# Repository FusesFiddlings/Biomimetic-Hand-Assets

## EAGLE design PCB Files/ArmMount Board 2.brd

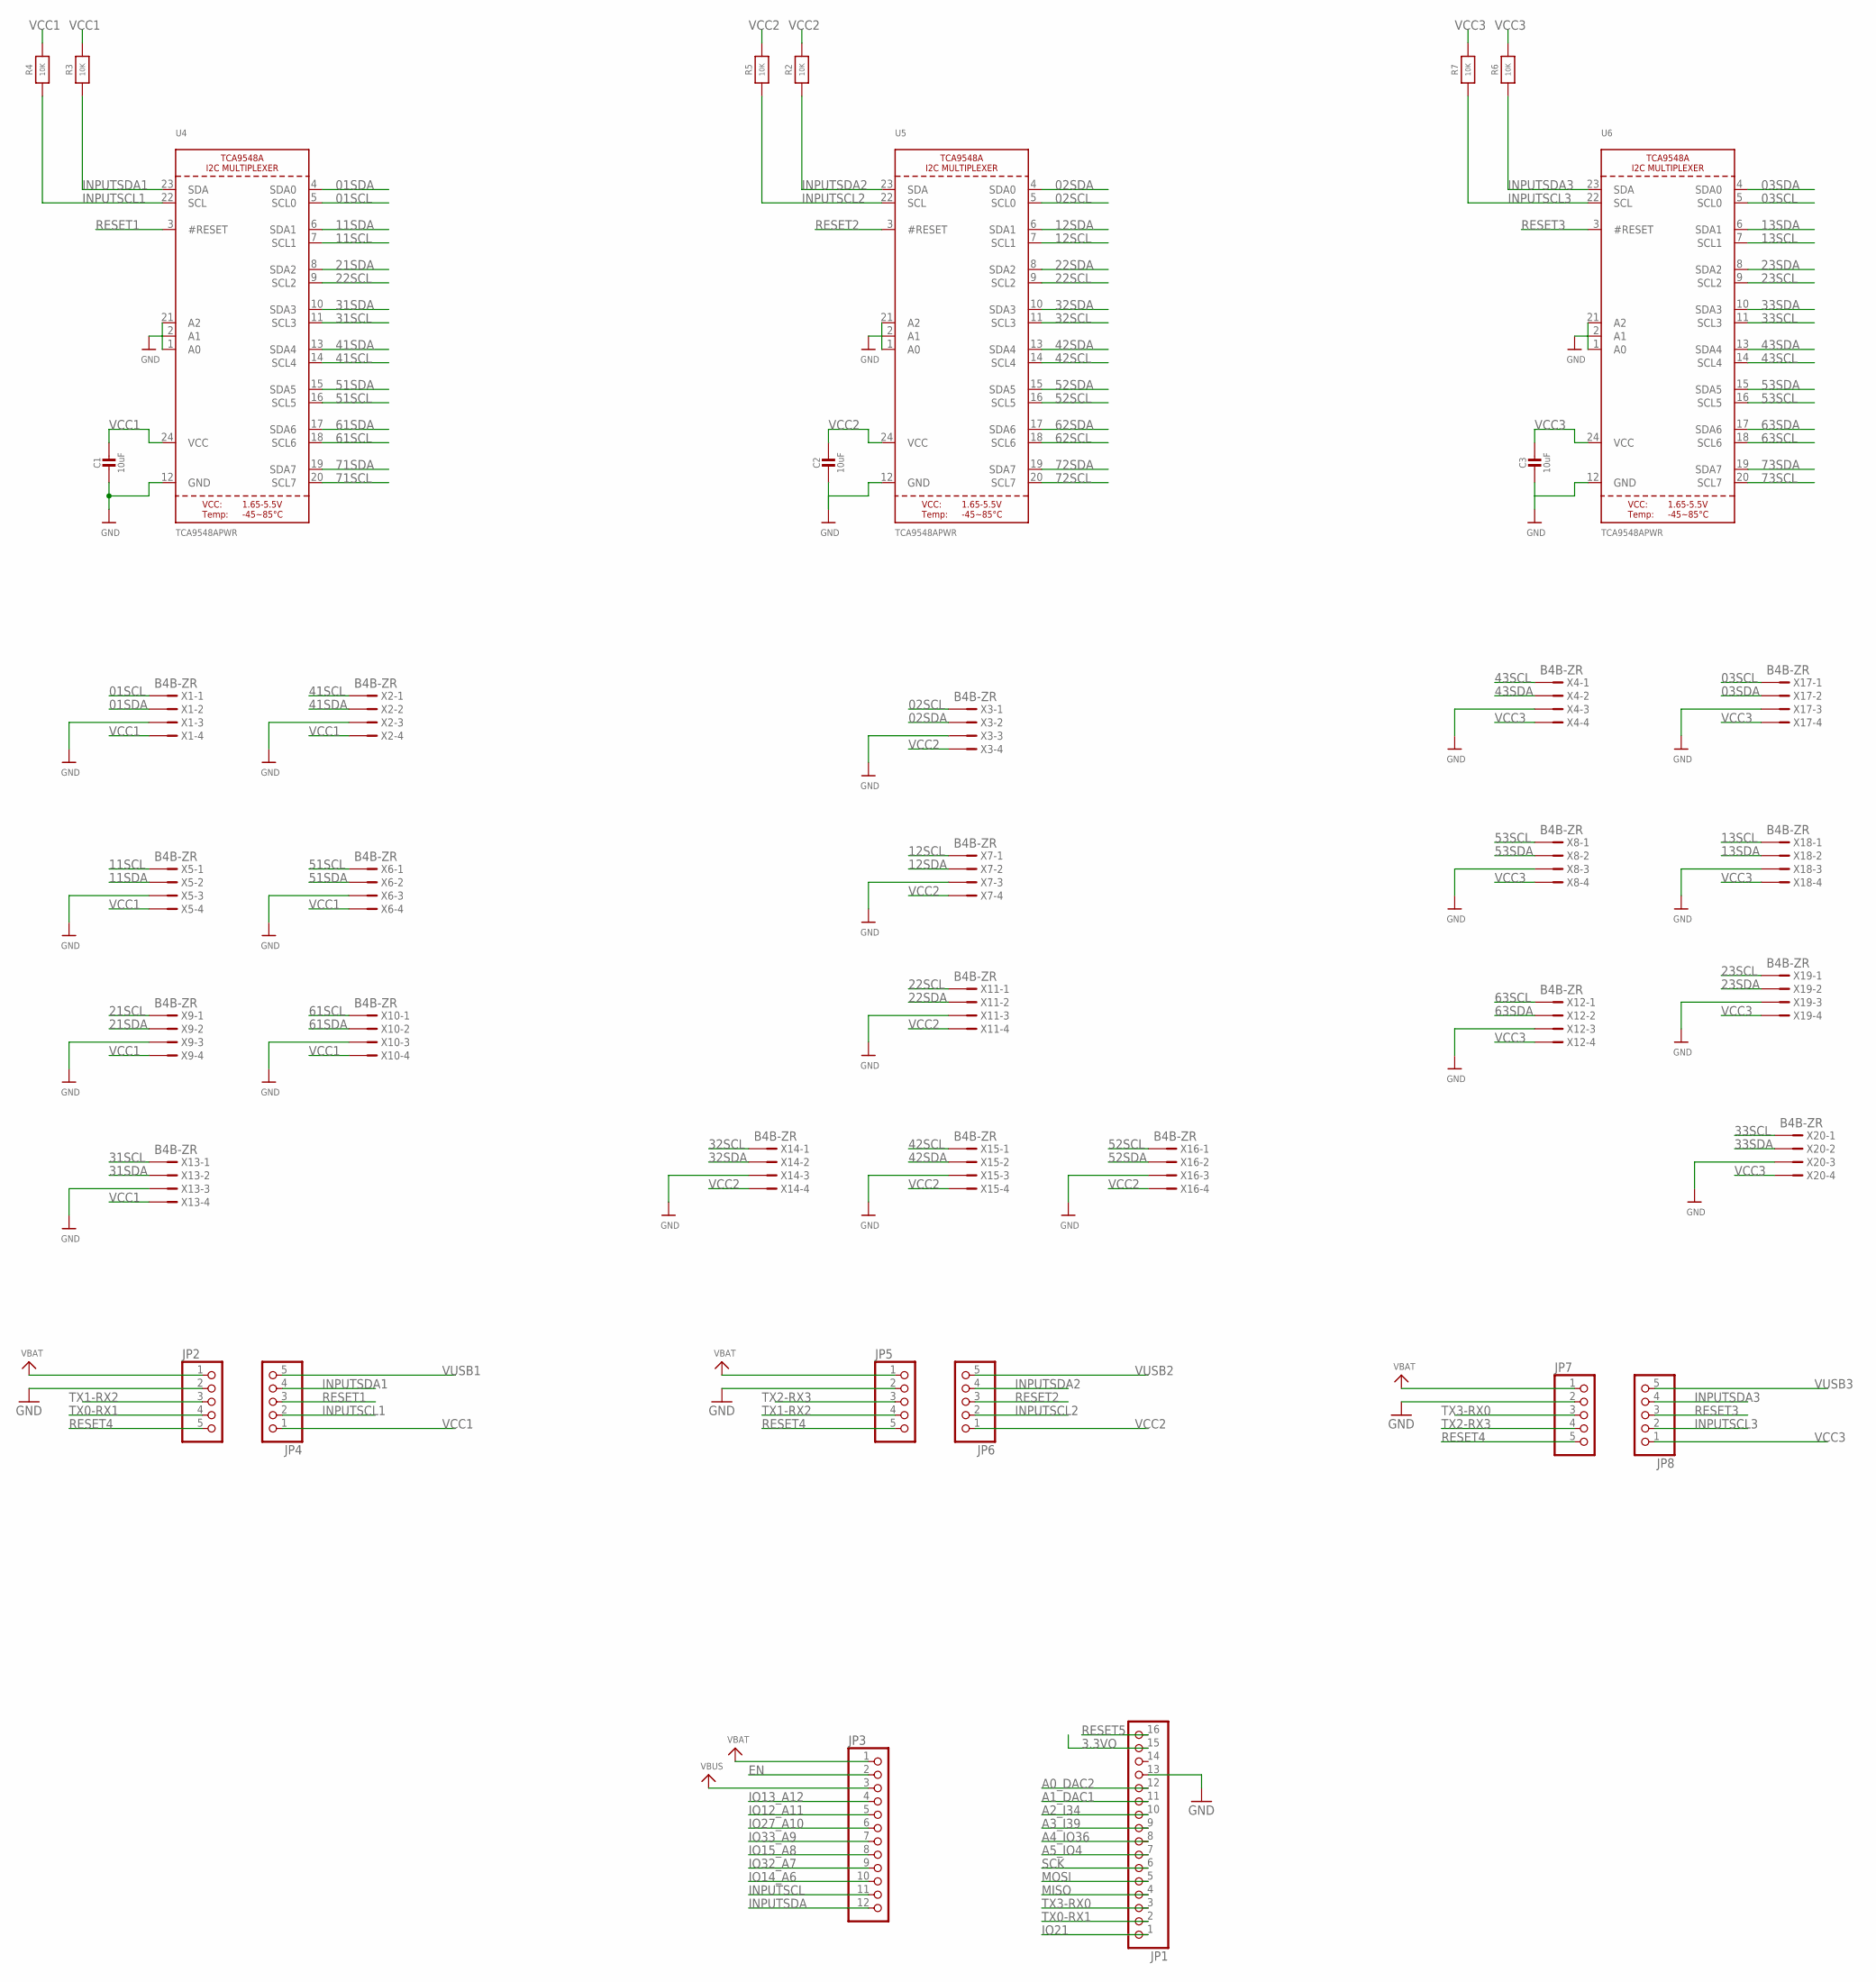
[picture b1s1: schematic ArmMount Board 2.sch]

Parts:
C1, C2, C3: 10uF; 0805-NO
JP1: HEADER-1X16_MIN; 1X16_ROUND_MIN
JP2, JP4, JP5, JP6, JP7, JP8: HEADER-1X576MIL; 1X05_ROUND_76
JP3: HEADER-1X12_MIN; 1X12_ROUND_MIN
R2, R3, R4, R5, R6, R7: 10K; 0805-NO
U4, U5, U6: TCA9548APWR; TSSOP24
X1, X2, X3, X4, X5, X6, X7, X8, X9, X10, X11, X12, X13, X14, X15, X16, X17, X18, X19, X20: B4B-ZR

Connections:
01SCL: U4.5 (SCL0), X1.1
01SDA: U4.4 (SDA0), X1.2
02SCL: U5.5 (SCL0), X3.1
02SDA: U5.4 (SDA0), X3.2
3.3VO: JP1.15
03SCL: U6.5 (SCL0), X17.1
03SDA: U6.4 (SDA0), X17.2
11SCL: U4.7 (SCL1), X5.1
11SDA: U4.6 (SDA1), X5.2
12SCL: U5.7 (SCL1), X7.1
12SDA: U5.6 (SDA1), X7.2
13SCL: U6.7 (SCL1), X18.1
13SDA: U6.6 (SDA1), X18.2
21SCL: X9.1
21SDA: U4.8 (SDA2), X9.2
22SCL: U4.9 (SCL2), U5.9 (SCL2), X11.1
22SDA: U5.8 (SDA2), X11.2
23SCL: U6.9 (SCL2), X19.1
23SDA: U6.8 (SDA2), X19.2
31SCL: U4.11 (SCL3), X13.1
31SDA: U4.10 (SDA3), X13.2
32SCL: U5.11 (SCL3), X14.1
32SDA: U5.10 (SDA3), X14.2
33SCL: U6.11 (SCL3), X20.1
33SDA: U6.10 (SDA3), X20.2
41SCL: U4.14 (SCL4), X2.1
41SDA: U4.13 (SDA4), X2.2
42SCL: U5.14 (SCL4), X15.1
42SDA: U5.13 (SDA4), X15.2
43SCL: U6.14 (SCL4), X4.1
43SDA: U6.13 (SDA4), X4.2
51SCL: U4.16 (SCL5), X6.1
51SDA: U4.15 (SDA5), X6.2
52SCL: U5.16 (SCL5), X16.1
52SDA: U5.15 (SDA5), X16.2
53SCL: U6.16 (SCL5), X8.1
53SDA: U6.15 (SDA5), X8.2
61SCL: U4.18 (SCL6), X10.1
61SDA: U4.17 (SDA6), X10.2
62SCL: U5.18 (SCL6)
62SDA: U5.17 (SDA6)
63SCL: U6.18 (SCL6), X12.1
63SDA: U6.17 (SDA6), X12.2
71SCL: U4.20 (SCL7)
71SDA: U4.19 (SDA7)
72SCL: U5.20 (SCL7)
72SDA: U5.19 (SDA7)
73SCL: U6.20 (SCL7)
73SDA: U6.19 (SDA7)
A0_DAC2: JP1.12
A1_DAC1: JP1.11
A2_I34: JP1.10
A3_I39: JP1.9
A4_IO36: JP1.8
A5_IO4: JP1.7
EN: JP3.2
GND: C1.2, C2.2, C3.2, JP1.13, JP2.2, JP5.2, JP7.2, U4.1 (A0), U4.2 (A1), U4.12 (GND), U4.21 (A2), U5.1 (A0), U5.2 (A1), U5.12 (GND), U5.21 (A2), U6.1 (A0), U6.2 (A1), U6.12 (GND), U6.21 (A2), X1.3, X2.3, X3.3, X4.3, X5.3, X6.3, X7.3, X8.3, X9.3, X10.3, X11.3, X12.3, X13.3, X14.3, X15.3, X16.3, X17.3, X18.3, X19.3, X20.3
INPUTSCL: JP3.11
INPUTSCL1: JP4.2, R4.1, U4.22 (SCL)
INPUTSCL2: JP6.2, R5.1, U5.22 (SCL)
INPUTSCL3: JP8.2, R7.1, U6.22 (SCL)
INPUTSDA: JP3.12
INPUTSDA1: JP4.4, R3.1, U4.23 (SDA)
INPUTSDA2: JP6.4, R2.1, U5.23 (SDA)
INPUTSDA3: JP8.4, R6.1, U6.23 (SDA)
IO12_A11: JP3.5
IO13_A12: JP3.4
IO14_A6: JP3.10
IO15_A8: JP3.8
IO21: JP1.1
IO27_A10: JP3.6
IO32_A7: JP3.9
IO33_A9: JP3.7
MISO: JP1.4
MOSI: JP1.5
RESET1: JP4.3, U4.3 (#RESET)
RESET2: JP6.3, U5.3 (#RESET)
RESET3: JP8.3, U6.3 (#RESET)
RESET4: JP2.5, JP5.5, JP7.5
RESET5: JP1.16
SCK: JP1.6
TX0-RX1: JP1.2, JP2.4
TX1-RX2: JP2.3, JP5.4
TX2-RX3: JP5.3, JP7.4
TX3-RX0: JP1.3, JP7.3
VBAT: JP2.1, JP3.1, JP5.1, JP7.1
VBUS: JP3.3
VCC1: C1.1, JP4.1, R3.2, R4.2, U4.24 (VCC), X1.4, X2.4, X5.4, X6.4, X9.4, X10.4, X13.4
VCC2: C2.1, JP6.1, R2.2, R5.2, U5.24 (VCC), X3.4, X7.4, X11.4, X14.4, X15.4, X16.4
VCC3: C3.1, JP8.1, R6.2, R7.2, U6.24 (VCC), X4.4, X8.4, X12.4, X17.4, X18.4, X19.4, X20.4
VUSB1: JP4.5
VUSB2: JP6.5
VUSB3: JP8.5

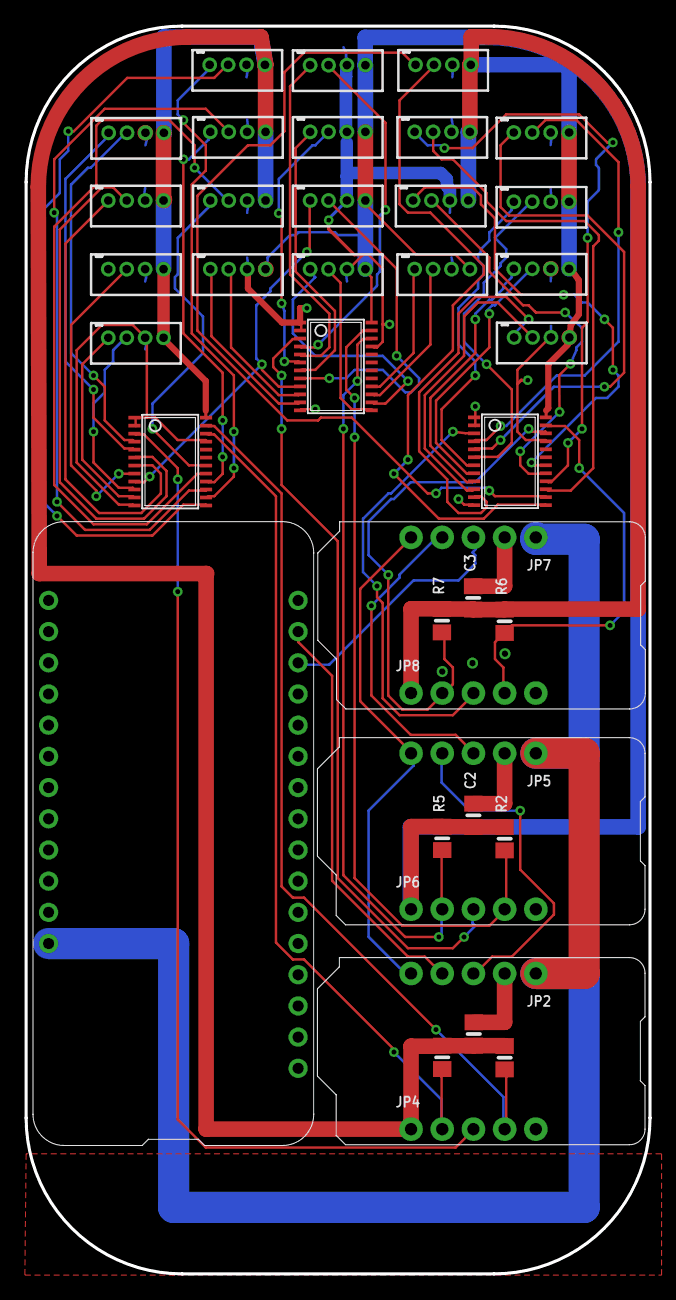
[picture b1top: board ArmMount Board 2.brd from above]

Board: 2 copper layers, 50.8 x 101.6 mm, 40 parts (0 on the bottom side), 58 nets.

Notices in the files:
parts and their libraries:
microbuilder: This work is placed in the public domain, and may be freely used for commercial and non-commercial work with the following conditions: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
